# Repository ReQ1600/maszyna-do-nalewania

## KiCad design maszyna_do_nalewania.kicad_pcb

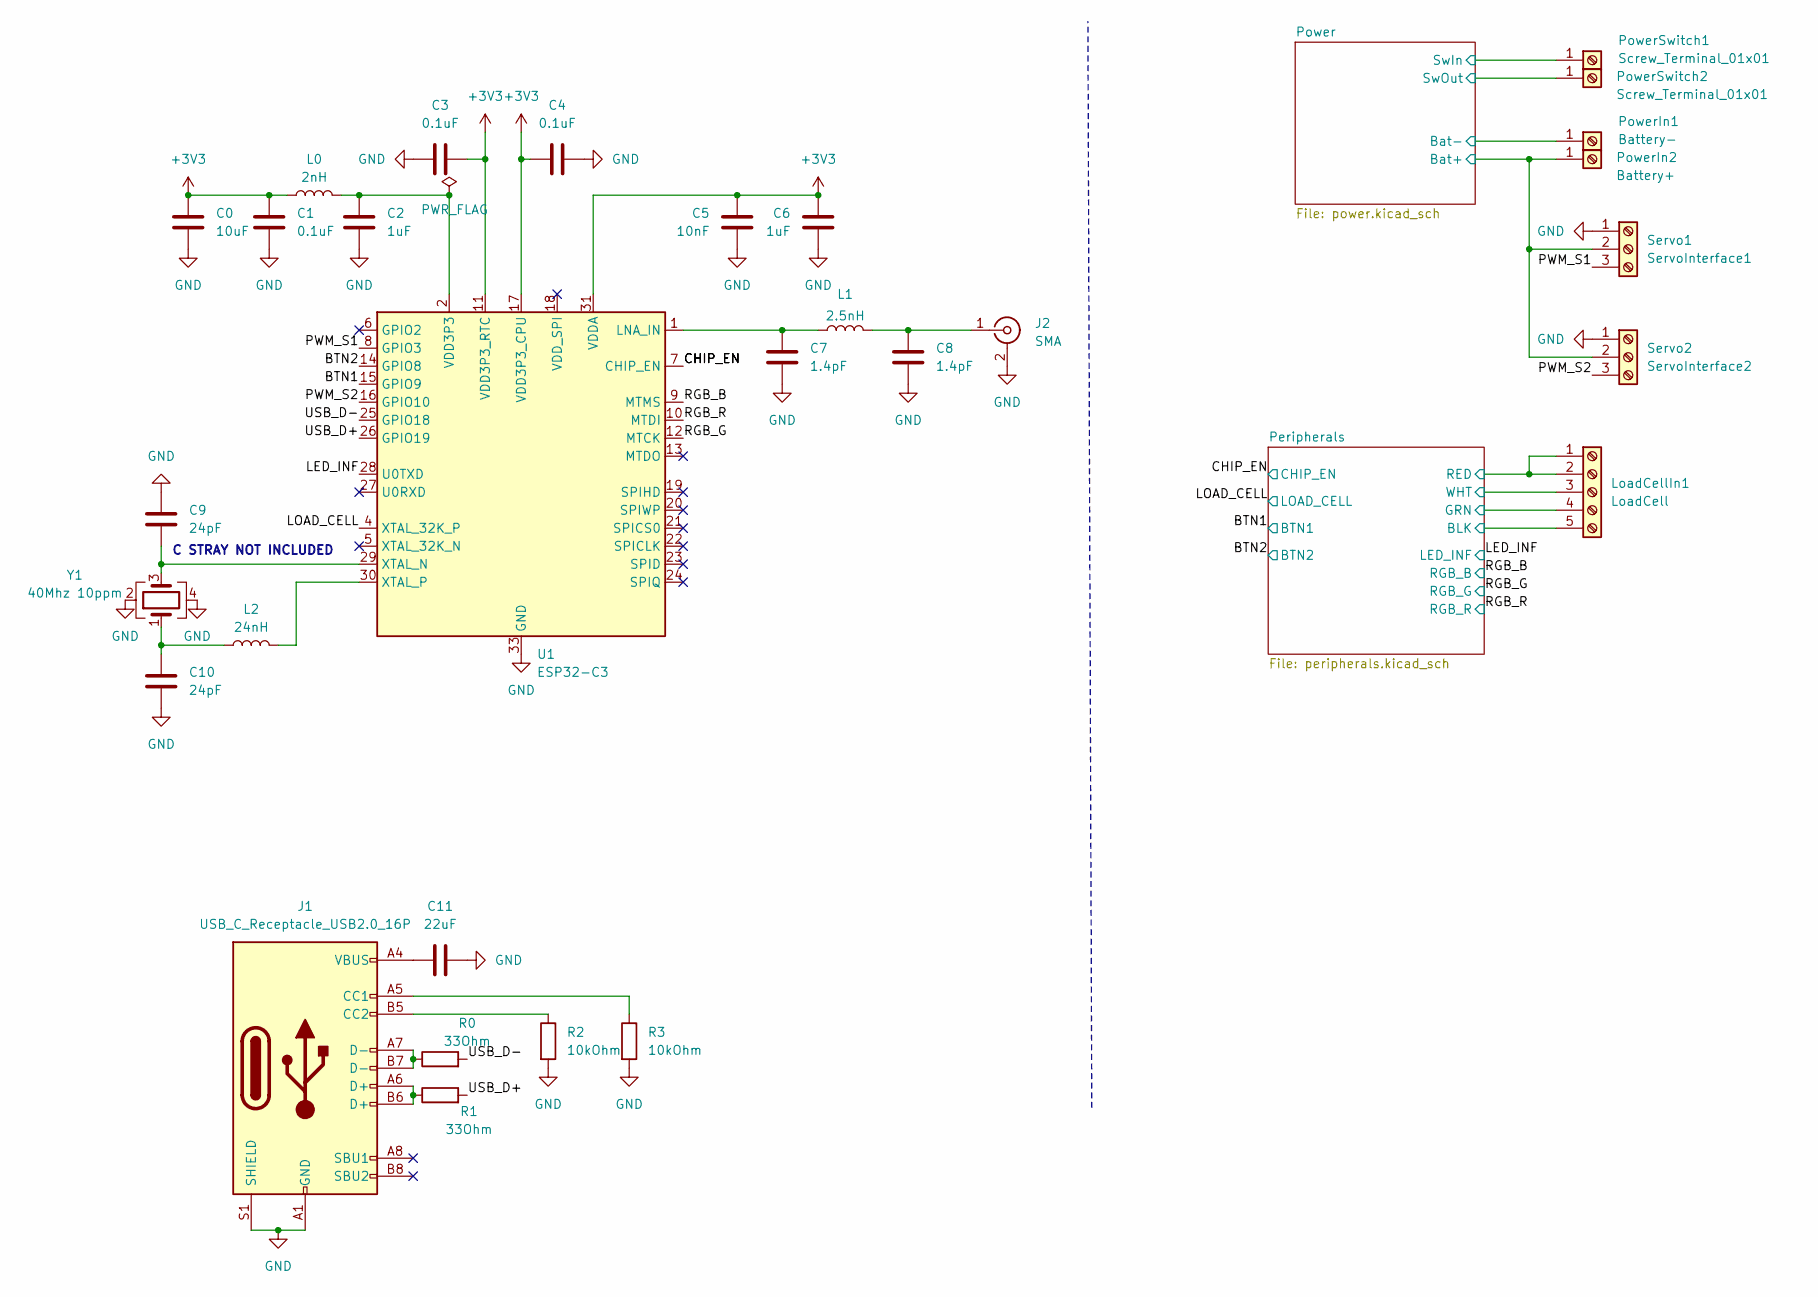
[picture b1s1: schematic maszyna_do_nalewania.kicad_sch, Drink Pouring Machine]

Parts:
C0: 10uF; C_0805_2012Metric_Pad1.18x1.45mm_HandSolder
C1, C3, C4: 0.1uF; C_0805_2012Metric_Pad1.18x1.45mm_HandSolder
C2, C6: 1uF; C_0805_2012Metric_Pad1.18x1.45mm_HandSolder
C5: 10nF; C_0805_2012Metric_Pad1.18x1.45mm_HandSolder
C7, C8: 1.4pF; C_0805_2012Metric_Pad1.18x1.45mm_HandSolder
C9, C10: 24pF; C_0402_1005Metric
C11: 22uF; C_0805_2012Metric_Pad1.18x1.45mm_HandSolder
J1: USB_C_Receptacle_USB2.0_16P; USB_C_Receptacle_HRO_TYPE-C-31-M-12
J2: SMA; SMA_Amphenol_132289_EdgeMount
L0: 2nH; L_0805_2012Metric_Pad1.05x1.20mm_HandSolder
L1: 2.5nH; L_0402_1005Metric_Pad0.77x0.64mm_HandSolder
L2: 24nH; L_0402_1005Metric_Pad0.77x0.64mm_HandSolder
LoadCellIn1: LoadCell; TerminalBlock_MetzConnect_Type059_RT06305HBWC_1x05_P3.50mm_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
PowerIn1: Battery-; TerminalBlock_MetzConnect_360271_1x01_Horizontal_ScrewM3.0_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
PowerIn2: Battery+; TerminalBlock_MetzConnect_360271_1x01_Horizontal_ScrewM3.0_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
PowerSwitch1, PowerSwitch2: Screw_Terminal_01x01; TerminalBlock_MetzConnect_360271_1x01_Horizontal_ScrewM3.0_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
R0, R1: 33Ohm; R_0402_1005Metric
R2, R3: 10kOhm; R_0402_1005Metric_Pad0.72x0.64mm_HandSolder
Servo1: ServoInterface1; TerminalBlock_MaiXu_MX126-5.0-03P_1x03_P5.00mm
Servo2: ServoInterface2; TerminalBlock_MaiXu_MX126-5.0-03P_1x03_P5.00mm
U1: ESP32-C3; QFN-32-1EP_5x5mm_P0.5mm_EP3.7x3.7mm
Y1: 40Mhz 10ppm; Crystal_SMD_2016-4Pin_2.0x1.6mm

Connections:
+3V3: C0.2, C1.2, C3.2, C4.1, C5.2, C6.2, L0.1, U1.11 (VDD3P3_RTC), U1.17 (VDD3P3_CPU), U1.31 (VDDA), U1.32 (VDDA); also elsewhere on the board
+6V: LoadCellIn1.1, LoadCellIn1.2; also elsewhere on the board
/BTN1: U1.15 (GPIO9); also elsewhere on the board
/BTN2: U1.14 (GPIO8); also elsewhere on the board
/CHIP_EN: U1.7 (CHIP_EN); also elsewhere on the board
/LED_INF: U1.28 (U0TXD); also elsewhere on the board
/LOAD_CELL: U1.4 (XTAL_32K_P); also elsewhere on the board
/PWM_S1: Servo1.3, U1.8 (GPIO3)
/PWM_S2: Servo2.3, U1.16 (GPIO10)
/Peripherals/GRN: LoadCellIn1.4; also elsewhere on the board
/Peripherals/WHT: LoadCellIn1.3; also elsewhere on the board
/Power/Bat+: PowerIn2.1, Servo1.2, Servo2.2; also elsewhere on the board
/Power/Bat-: PowerIn1.1, PowerSwitch1.1
/RGB_B: U1.9 (MTMS); also elsewhere on the board
/RGB_G: U1.12 (MTCK); also elsewhere on the board
/RGB_R: U1.10 (MTDI); also elsewhere on the board
/USB_D+: R1.2, U1.26 (GPIO19)
/USB_D-: R0.2, U1.25 (GPIO18)
GND: C0.1, C1.1, C2.1, C3.1, C4.2, C5.1, C6.1, C7.1, C8.1, C9.2, C10.1, C11.1, J1.A1 (GND), J1.A12 (GND), J1.B1 (GND), J1.B12 (GND), J1.S1 (SHIELD), J2.2 (Ext), LoadCellIn1.5, PowerSwitch2.1, R2.2, R3.2, Servo1.1, Servo2.1, U1.33 (GND), Y1.2, Y1.4; also elsewhere on the board
unnamed: C2.2, L0.2, U1.2 (VDD3P3), U1.3 (VDD3P3)
unnamed: C10.2, L2.1, Y1.1
unnamed: C11.2, J1.A4 (VBUS), J1.A9 (VBUS), J1.B4 (VBUS), J1.B9 (VBUS)
unnamed: J1.A5 (CC1), R3.1
unnamed: J1.B5 (CC2), R2.1
unnamed: J1.A6 (D+), J1.B6 (D+), R1.1
unnamed: J1.A7 (D-), J1.B7 (D-), R0.1
unnamed: C8.2, J2.1 (In), L1.2
unnamed: C7.2, L1.1, U1.1 (LNA_IN)
unnamed: C9.1, U1.29 (XTAL_N), Y1.3
unnamed: L2.2, U1.30 (XTAL_P)

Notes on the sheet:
C STRAY NOT INCLUDED

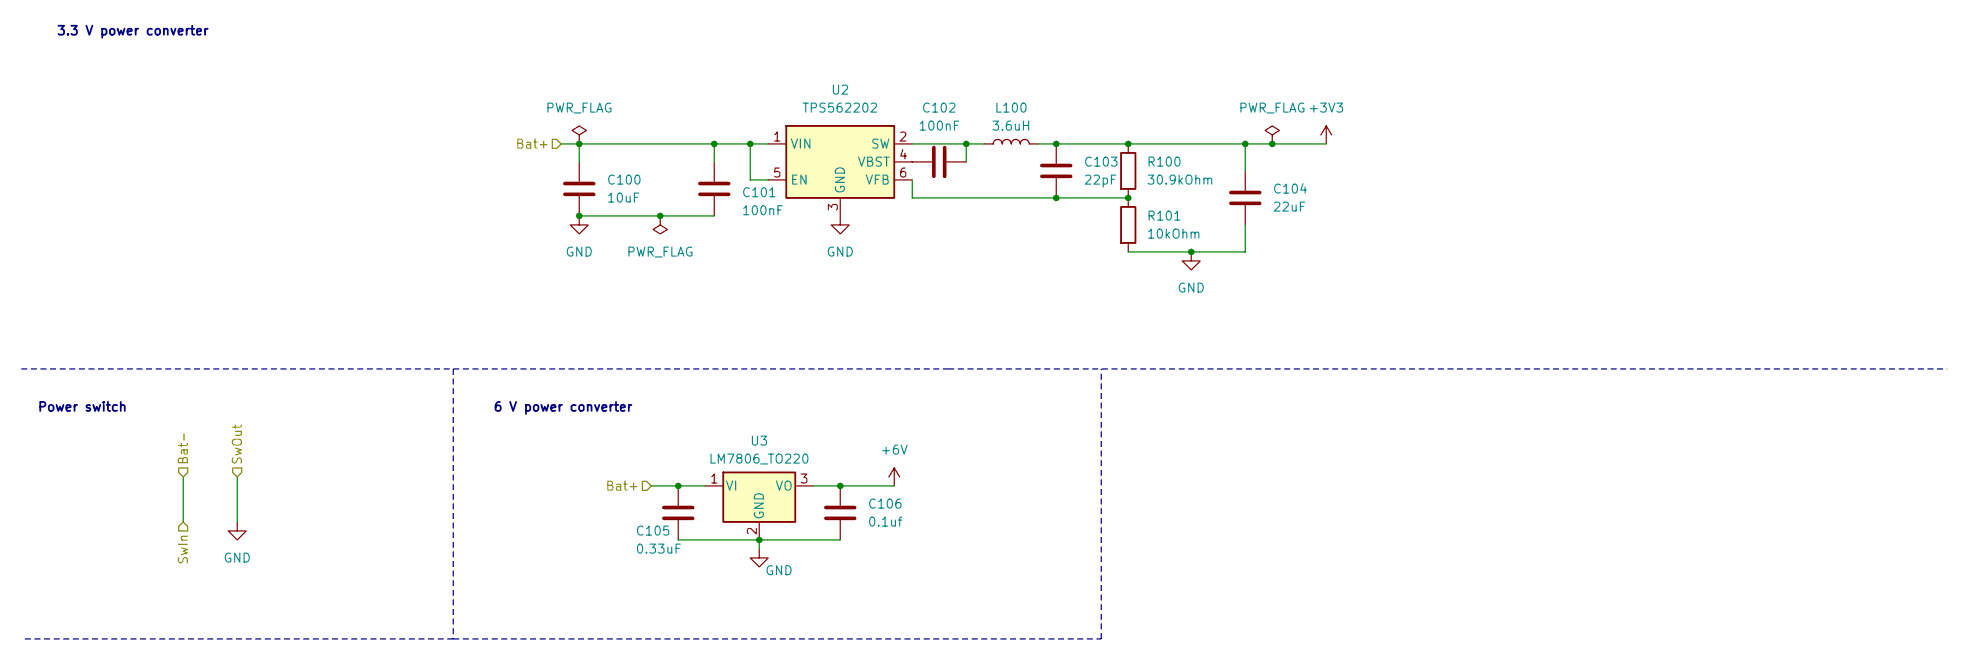
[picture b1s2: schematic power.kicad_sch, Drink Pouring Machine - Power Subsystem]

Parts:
C100: 10uF; C_0805_2012Metric_Pad1.18x1.45mm_HandSolder
C101: 100nF; C_0402_1005Metric_Pad0.74x0.62mm_HandSolder
C102: 100nF; C_0603_1608Metric_Pad1.08x0.95mm_HandSolder
C103: 22pF; C_0201_0603Metric_Pad0.64x0.40mm_HandSolder
C104: 22uF; C_0805_2012Metric_Pad1.18x1.45mm_HandSolder
C105: 0.33uF; C_0402_1005Metric_Pad0.74x0.62mm_HandSolder
C106: 0.1uf; C_0402_1005Metric_Pad0.74x0.62mm_HandSolder
L100: 3.6uH; L_Bourns-SRN8040_8x8.15mm
R100: 30.9kOhm; R_0402_1005Metric_Pad0.72x0.64mm_HandSolder
R101: 10kOhm; R_0402_1005Metric_Pad0.72x0.64mm_HandSolder
U2: TPS562202; SOT-563
U3: LM7806_TO220; TO-220-3_Vertical

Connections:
+3V3: C103.1, C104.1, L100.2, R100.1; also elsewhere on the board
+6V: C106.1, U3.3 (VO); also elsewhere on the board
/Power/Bat+: C100.1, C101.1, C105.1, U2.1 (VIN), U2.5 (EN), U3.1 (VI); also elsewhere on the board
GND: C100.2, C101.2, C104.2, C105.2, C106.2, R101.2, U2.3 (GND), U3.2 (GND); also elsewhere on the board
unnamed: C102.2, L100.1, U2.2 (SW)
unnamed: C102.1, U2.4 (VBST)
unnamed: C103.2, R100.2, R101.1, U2.6 (VFB)

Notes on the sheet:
6 V power converter
Power switch
3.3 V power converter

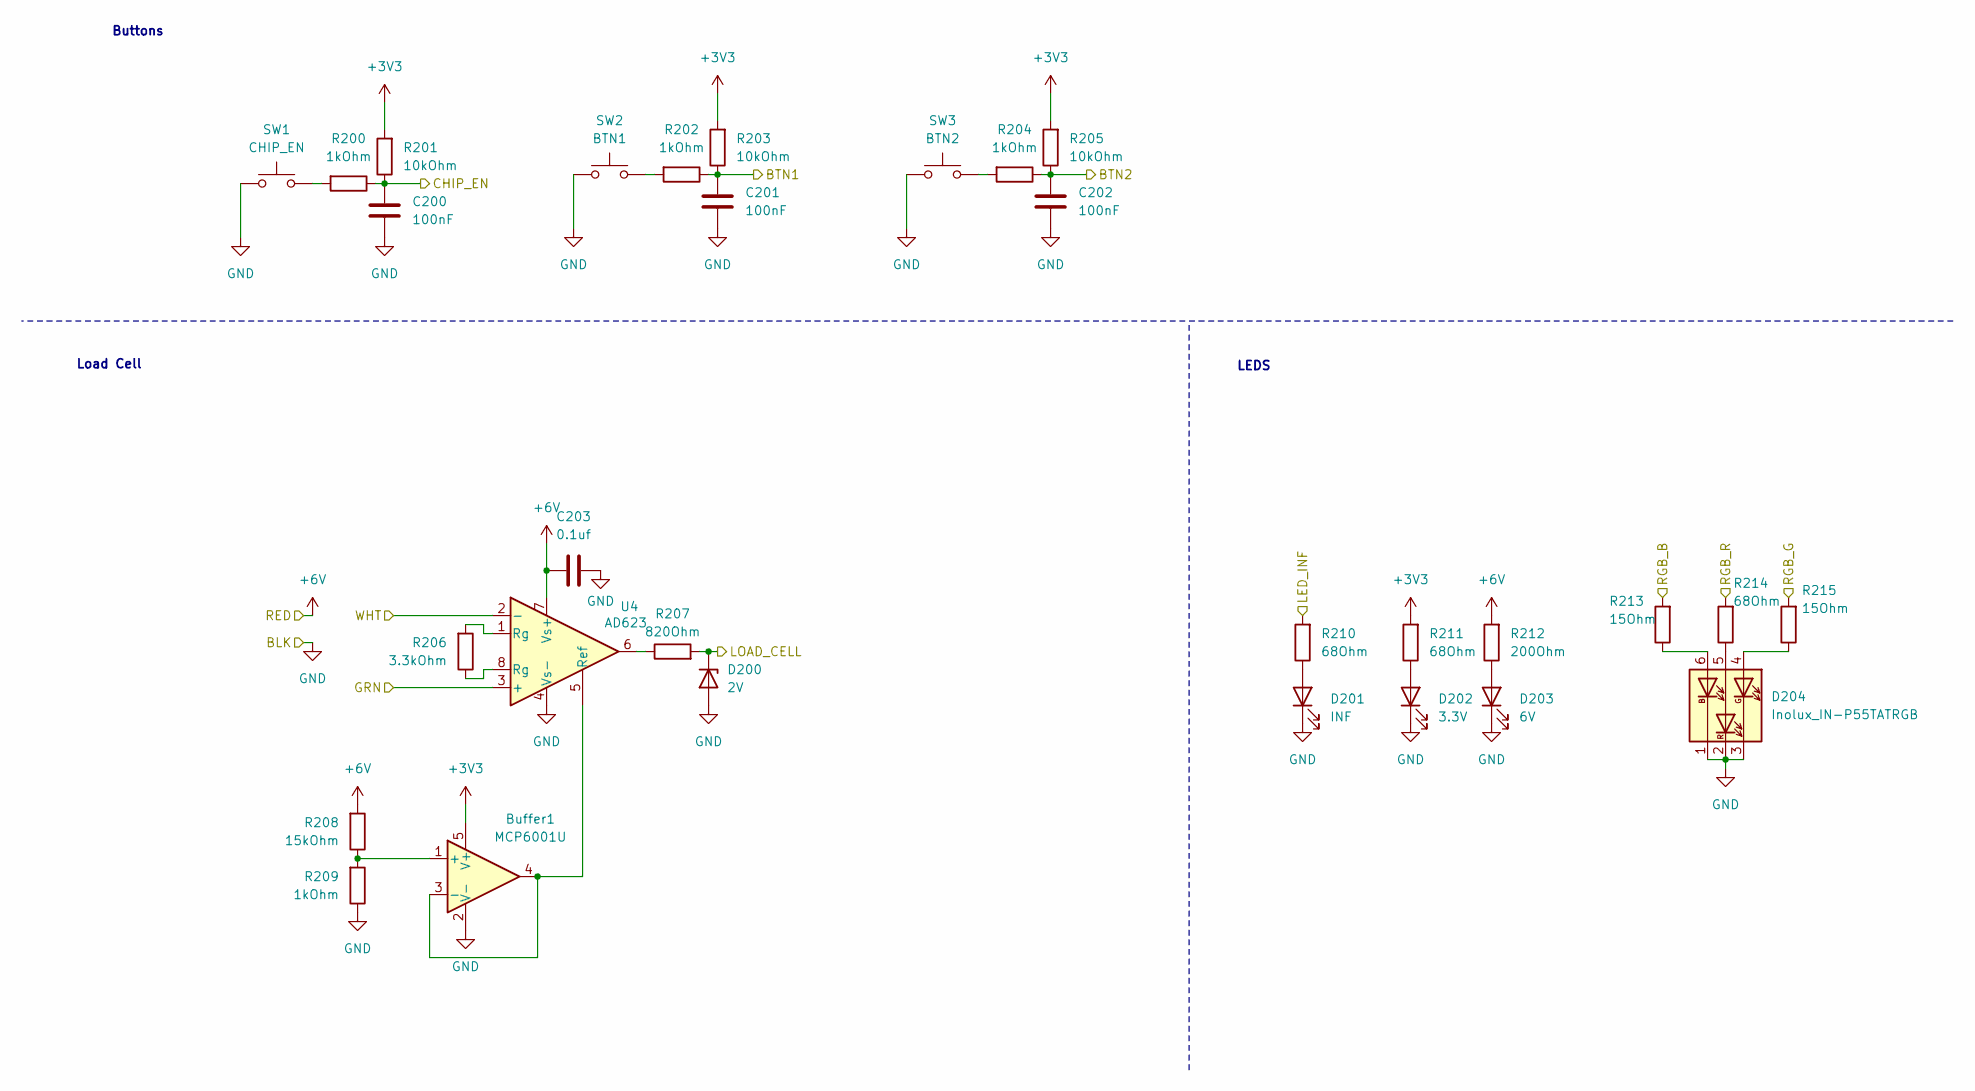
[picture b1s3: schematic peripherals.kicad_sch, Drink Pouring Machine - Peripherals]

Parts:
Buffer1: MCP6001U; SOT-23-5
C200, C201, C202: 100nF; C_0805_2012Metric_Pad1.18x1.45mm_HandSolder
C203: 0.1uf; C_0402_1005Metric_Pad0.74x0.62mm_HandSolder
D200: 2V; D_0402_1005Metric_Pad0.77x0.64mm_HandSolder
D201: INF; LED_0402_1005Metric
D202: 3.3V; LED_0402_1005Metric
D203: 6V; LED_0402_1005Metric
D204: Inolux_IN-P55TATRGB; LED_Inolux_IN-P55TATRGB_PLCC6_5.0x5.5mm_P1.8mm
R200, R202, R204, R209: 1kOhm; R_0402_1005Metric_Pad0.72x0.64mm_HandSolder
R201, R203, R205: 10kOhm; R_0402_1005Metric_Pad0.72x0.64mm_HandSolder
R206: 3.3kOhm; R_0402_1005Metric_Pad0.72x0.64mm_HandSolder
R207: 820Ohm; R_0402_1005Metric_Pad0.72x0.64mm_HandSolder
R208: 15kOhm; R_0402_1005Metric_Pad0.72x0.64mm_HandSolder
R210, R211, R214: 68Ohm; R_0402_1005Metric_Pad0.72x0.64mm_HandSolder
R212: 200Ohm; R_0402_1005Metric_Pad0.72x0.64mm_HandSolder
R213, R215: 15Ohm; R_0402_1005Metric_Pad0.72x0.64mm_HandSolder
SW1: CHIP_EN; SW_SPST_Omron_B3FS-101xP
SW2: BTN1; SW_SPST_Omron_B3FS-101xP
SW3: BTN2; SW_SPST_Omron_B3FS-101xP
U4: AD623; SOIC-8_3.9x4.9mm_P1.27mm

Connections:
+3V3: Buffer1.5 (V+), R201.2, R203.2, R205.2, R211.2; also elsewhere on the board
+6V: C203.1, R208.2, R212.2, U4.7 (Vs+); also elsewhere on the board
/BTN1: C201.1, R202.1, R203.1; also elsewhere on the board
/BTN2: C202.1, R204.1, R205.1; also elsewhere on the board
/CHIP_EN: C200.1, R200.1, R201.1; also elsewhere on the board
/LED_INF: R210.2; also elsewhere on the board
/LOAD_CELL: D200.1 (K), R207.2; also elsewhere on the board
/Peripherals/GRN: U4.3 (+); also elsewhere on the board
/Peripherals/WHT: U4.2 (-); also elsewhere on the board
/RGB_B: R213.2; also elsewhere on the board
/RGB_G: R215.2; also elsewhere on the board
/RGB_R: R214.2; also elsewhere on the board
GND: Buffer1.2 (V-), C200.2, C201.2, C202.2, C203.2, D200.2 (A), D201.1 (K), D202.1 (K), D203.1 (K), D204.1 (KB), D204.2 (KR), D204.3 (KG), R209.1, SW1.1, SW2.1, SW3.1, U4.4 (Vs-); also elsewhere on the board
unnamed: Buffer1.1 (+), R208.1, R209.2
unnamed: Buffer1.3 (-), Buffer1.4, U4.5 (Ref)
unnamed: D201.2 (A), R210.1
unnamed: D202.2 (A), R211.1
unnamed: D203.2 (A), R212.1
unnamed: D204.6 (AB), R213.1
unnamed: D204.4 (AG), R215.1
unnamed: D204.5 (AR), R214.1
unnamed: R200.2, SW1.2
unnamed: R202.2, SW2.2
unnamed: R204.2, SW3.2
unnamed: R206.1, U4.8 (Rg)
unnamed: R206.2, U4.1 (Rg)
unnamed: R207.1, U4.6

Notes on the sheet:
Load Cell
LEDS
Buttons

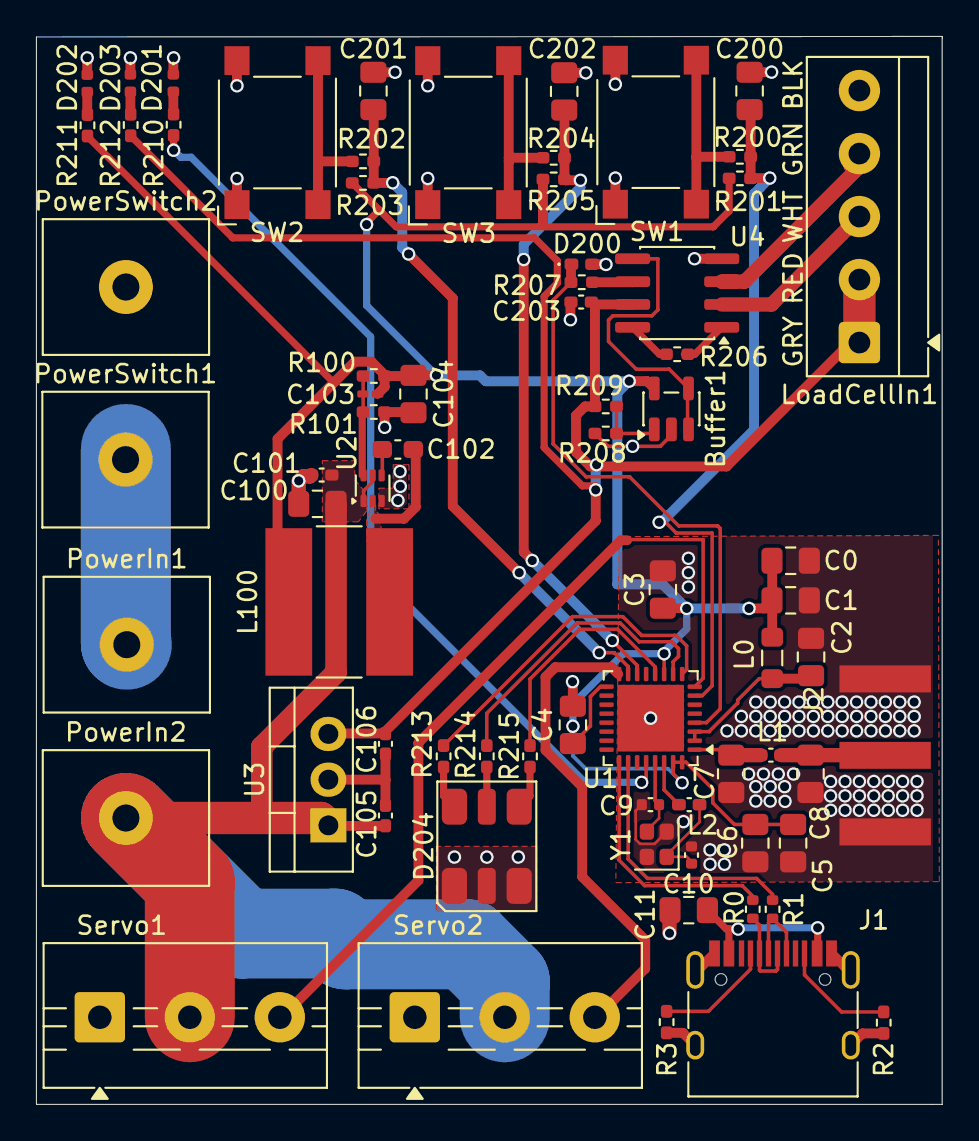
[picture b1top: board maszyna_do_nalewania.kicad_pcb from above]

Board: 2 copper layers, 50.3 x 59.3 mm, 72 parts (0 on the bottom side), 47 nets.

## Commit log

2025-11-23 init
2025-11-23 fix: set ad623 gain
2025-11-25 feat: led_inf connected, load cell overvoltage protection and antenna vals defined
2025-11-25 fix: added resistor to load cell overvoltage protection
2025-12-01 feat: added power button, name changes
2025-12-01 wip: pcb layout started
2025-12-15 feat: pcb almost done, added rgb led
2026-01-04 feat: silkscreen done
2026-01-05 fix: led resistor values, tensometer screw terminal
